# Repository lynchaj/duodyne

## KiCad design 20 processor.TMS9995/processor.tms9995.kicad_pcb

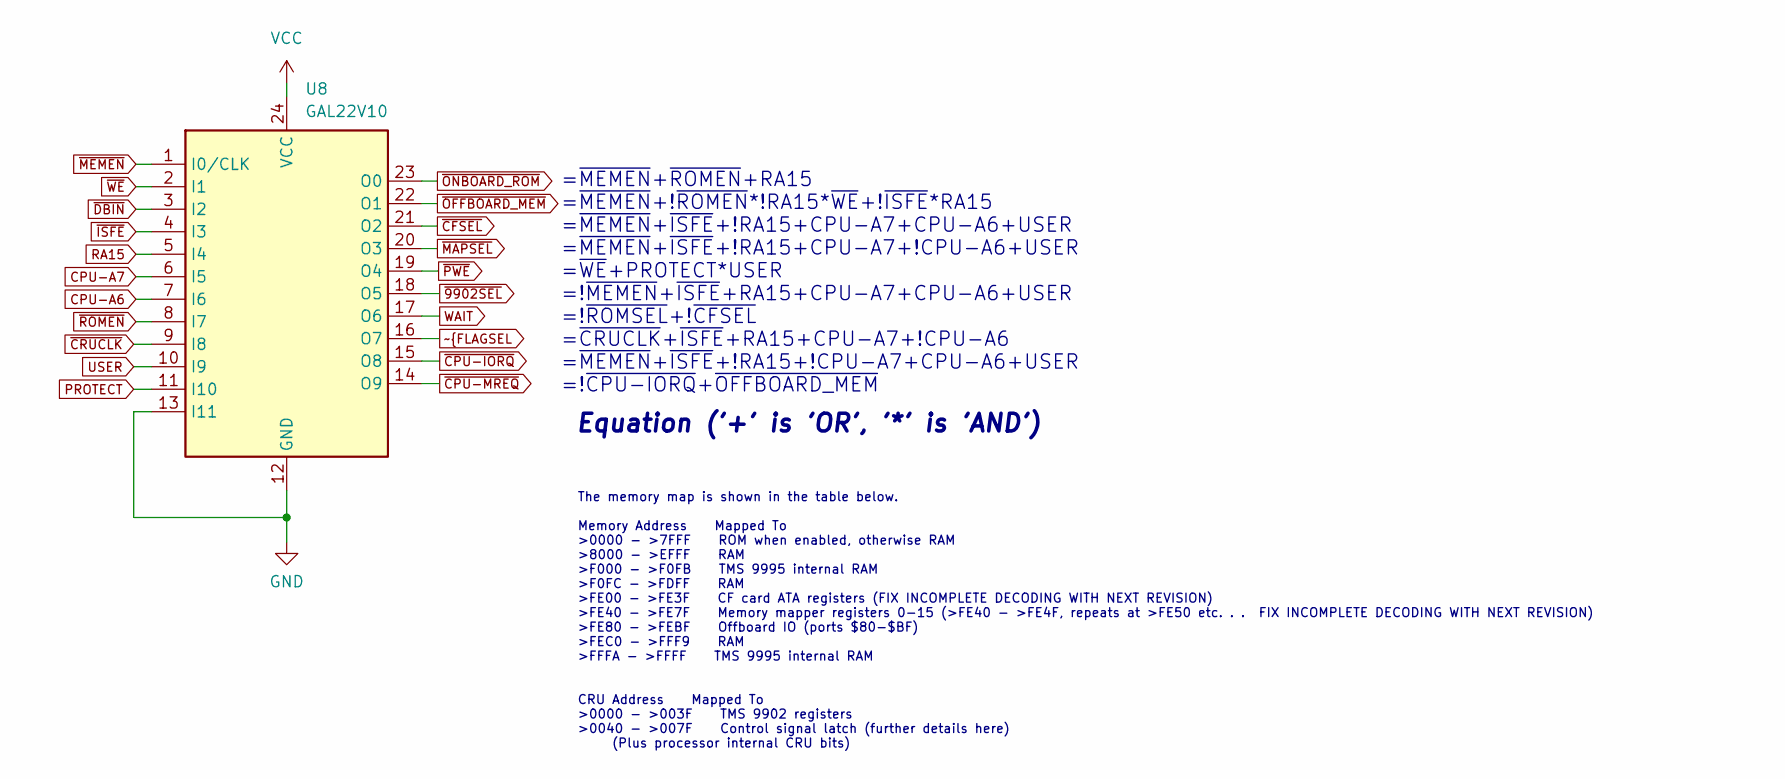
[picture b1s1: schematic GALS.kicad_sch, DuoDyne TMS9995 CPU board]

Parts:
U8: GAL22V10; DIP-24_W7.62mm_Socket_LongPads

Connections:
CPU-A6: U8.7 (I6); also elsewhere on the board
CPU-A7: U8.6 (I5); also elsewhere on the board
GND: U8.12 (GND), U8.13 (I11); also elsewhere on the board
PROTECT: U8.11 (I10); also elsewhere on the board
RA15: U8.5 (I4); also elsewhere on the board
USER: U8.10 (I9); also elsewhere on the board
VCC: U8.24 (VCC); also elsewhere on the board
WAIT: U8.17 (O6); also elsewhere on the board
~9902SEL: U8.18 (O5); also elsewhere on the board
~CFSEL: U8.21 (O2); also elsewhere on the board
~CPU-IORQ: U8.15 (O8); also elsewhere on the board
~CPU-MREQ: U8.14 (O9); also elsewhere on the board
~CRUCLK: U8.9 (I8); also elsewhere on the board
~DBIN: U8.3 (I2); also elsewhere on the board
~ISFE: U8.4 (I3); also elsewhere on the board
~MAPSEL: U8.20 (O3); also elsewhere on the board
~MEMEN: U8.1 (I0/CLK); also elsewhere on the board
~OFFBOARD_MEM: U8.22 (O1); also elsewhere on the board
~ONBOARD_ROM: U8.23 (O0); also elsewhere on the board
~PWE: U8.19 (O4); also elsewhere on the board
~ROMEN: U8.8 (I7); also elsewhere on the board
~WE: U8.2 (I1); also elsewhere on the board

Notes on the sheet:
=~{MEMEN}+~{ROMEN}+RA15 =~{MEMEN}+!~{ROMEN}*!RA15*~{WE}+!~{ISFE}*RA15 =~{MEMEN}+~{ISFE}+!RA15+CPU-A7+CPU-A6+USER =~{MEMEN}+~{ISFE}+!RA15+CPU-A7+!CPU-A6+USER =~{WE}+PROTECT*USER =!~{MEMEN}+~{ISFE}+RA15+CPU-A7+CPU-A6+USER =!~{ROMSEL}+!~{CFSEL} =~{CRUCLK}+~{ISFE}+RA15+CPU-A7+!CPU-A6 =~{MEMEN}+~{ISFE}+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
Equation ('+' is 'OR', '*' is 'AND')
The memory map is shown in the table below. Memory Address Mapped To >0000 - >7FFF ROM when enabled, otherwise RAM >8000 - >EFFF RAM >F000 - >F0FB TMS 9995 internal RAM >F0FC - >FDFF RAM >FE00 - >FE3F CF card ATA registers (FIX INCOMPLETE DECODING WITH NEXT REVISION) >FE40 - >FE7F Memory mapper reg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

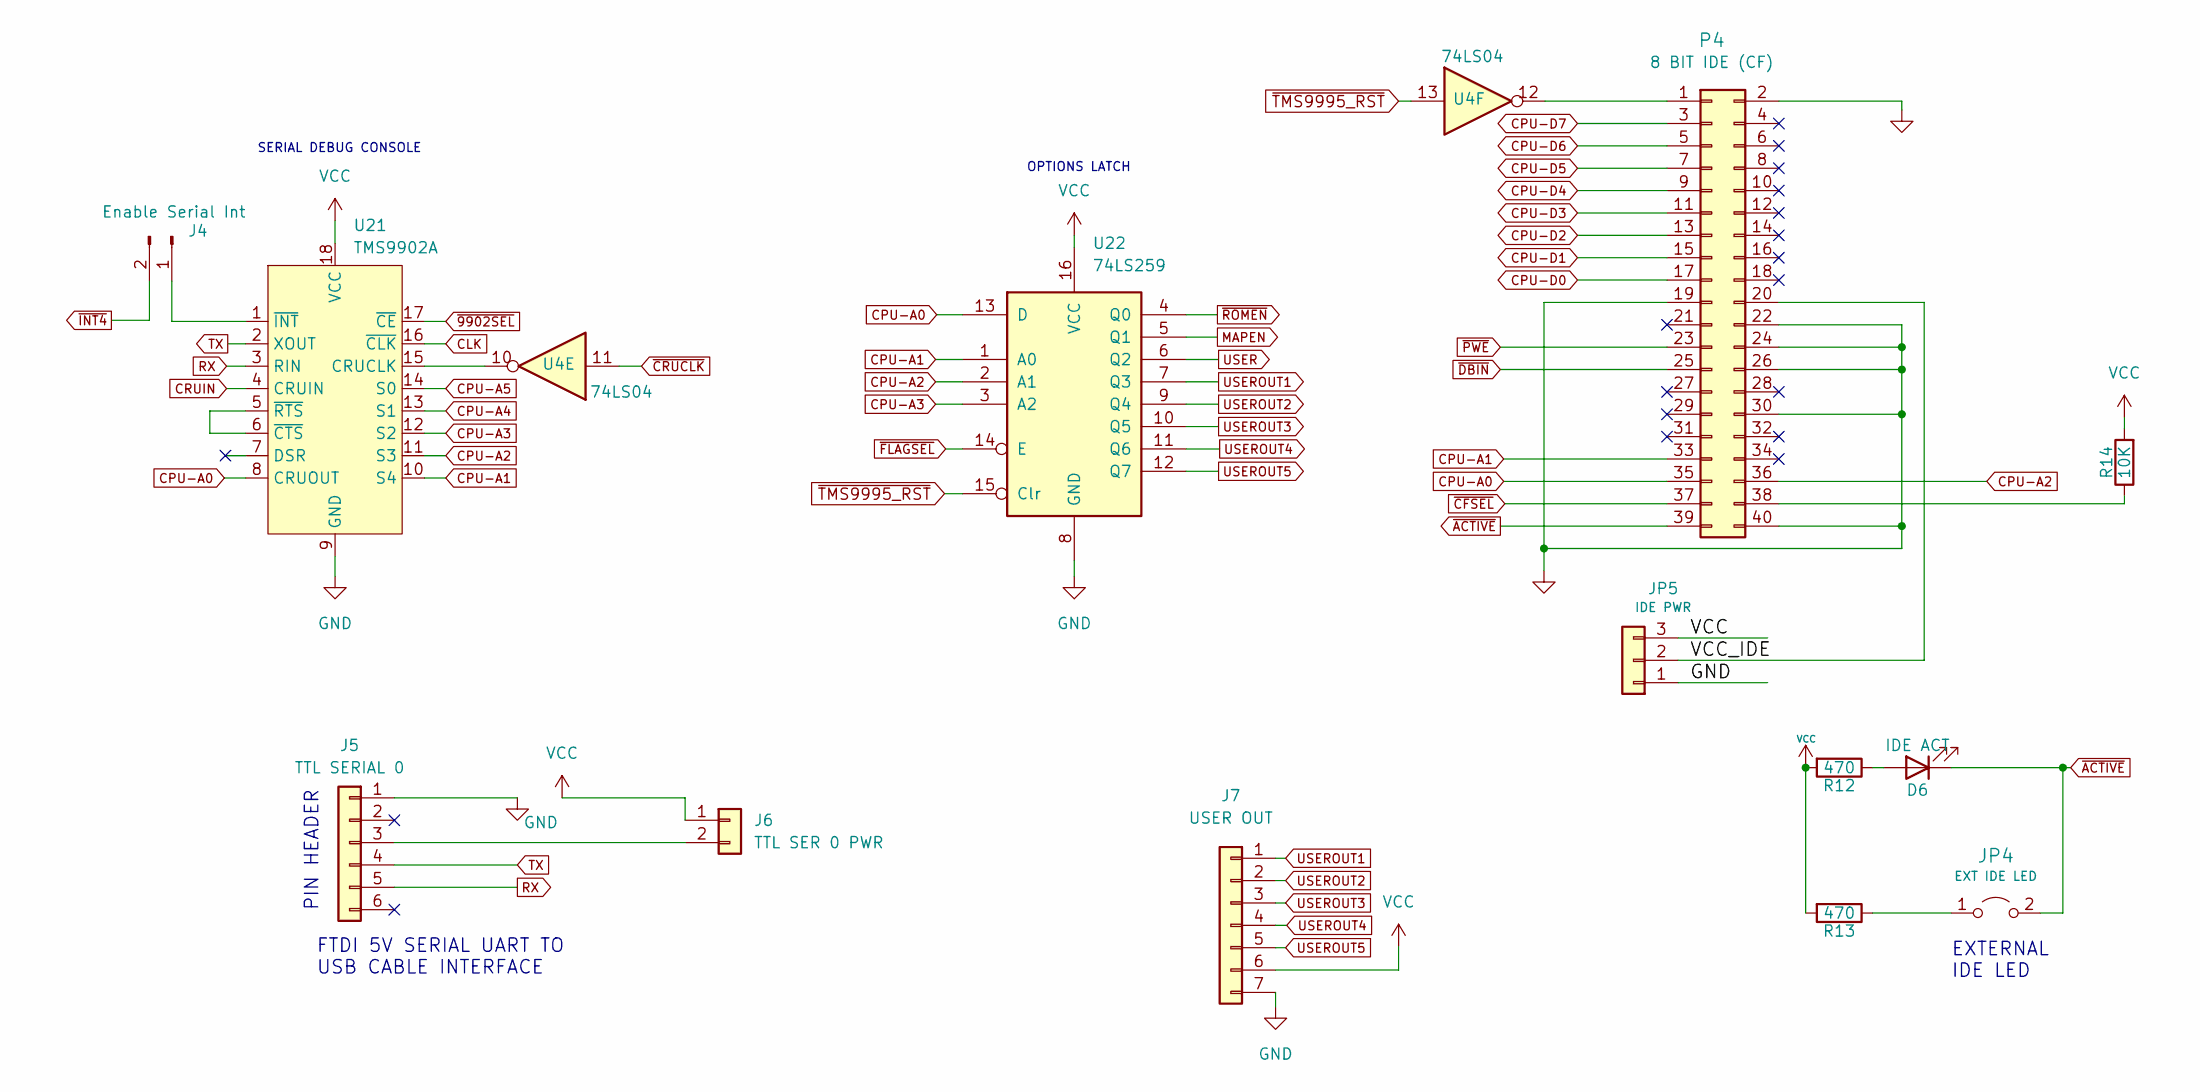
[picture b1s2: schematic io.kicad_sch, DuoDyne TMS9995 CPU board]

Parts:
D6: IDE ACT; LED_D3.0mm_Horizontal_O3.81mm_Z2.0mm
J4: Enable Serial Int; PinHeader_1x02_P2.54mm_Vertical
J5: TTL SERIAL 0; PinHeader_1x06_P2.54mm_Horizontal
J6: TTL SER 0 PWR; PinHeader_1x02_P2.54mm_Vertical
J7: USER OUT; PinHeader_1x07_P2.54mm_Horizontal
JP4: EXT IDE LED; PinHeader_1x02_P2.54mm_Vertical
JP5: IDE PWR; PinHeader_1x03_P2.54mm_Vertical
P4: 8 BIT IDE (CF); IDC-Header_2x20_P2.54mm_Horizontal
R12, R13: 470; R_Axial_DIN0207_L6.3mm_D2.5mm_P7.62mm_Horizontal
R14: 10K; R_Axial_DIN0207_L6.3mm_D2.5mm_P7.62mm_Horizontal
U4: 74LS04; DIP-14_W7.62mm_Socket_LongPads
U21: TMS9902A; DIP-18_W7.62mm_Socket_LongPads
U22: 74LS259; DIP-16_W7.62mm_Socket_LongPads

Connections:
/IO/VCC_IDE: JP5.2, P4.20
CLK: U21.16 (~CLK); also elsewhere on the board
CPU-A0: P4.35, U21.8 (CRUOUT), U22.13 (D); also elsewhere on the board
CPU-A1: P4.33, U21.10 (S4), U22.1 (A0); also elsewhere on the board
CPU-A2: P4.36, U21.11 (S3), U22.2 (A1); also elsewhere on the board
CPU-A3: U21.12 (S2), U22.3 (A2); also elsewhere on the board
CPU-A4: U21.13 (S1); also elsewhere on the board
CPU-A5: U21.14 (S0); also elsewhere on the board
CPU-D0: P4.17; also elsewhere on the board
CPU-D1: P4.15; also elsewhere on the board
CPU-D2: P4.13; also elsewhere on the board
CPU-D3: P4.11; also elsewhere on the board
CPU-D4: P4.9; also elsewhere on the board
CPU-D5: P4.7; also elsewhere on the board
CPU-D6: P4.5; also elsewhere on the board
CPU-D7: P4.3; also elsewhere on the board
CRUIN: U21.4 (CRUIN); also elsewhere on the board
GND: J5.1, J7.7, JP5.1, P4.2, P4.19, P4.22, P4.24, P4.26, P4.30, P4.40, U21.9 (GND), U22.8 (GND); also elsewhere on the board
MAPEN: U22.5 (Q1); also elsewhere on the board
unnamed: D6.2 (A), R12.1
unnamed: J4.1, U21.1 (~INT)
unnamed: J5.3, J6.2
unnamed: JP4.1 (A), R13.1
unnamed: P4.1, U4.12
unnamed: P4.38, R14.1
unnamed: U21.5 (~RTS), U21.6 (~CTS)
unnamed: U4.10, U21.15 (CRUCLK)
RX: J5.5, U21.3 (RIN)
TX: J5.4, U21.2 (XOUT)
USER: U22.6 (Q2); also elsewhere on the board
USEROUT1: J7.1, U22.7 (Q3)
USEROUT2: J7.2, U22.9 (Q4)
USEROUT3: J7.3, U22.10 (Q5)
USEROUT4: J7.4, U22.11 (Q6)
USEROUT5: J7.5, U22.12 (Q7)
VCC: J6.1, J7.6, JP5.3, R12.2, R13.2, R14.2, U21.18 (VCC), U22.16 (VCC); also elsewhere on the board
~9902SEL: U21.17 (~CE); also elsewhere on the board
~ACTIVE: D6.1 (K), JP4.2 (B), P4.39
~CFSEL: P4.37; also elsewhere on the board
~CRUCLK: U4.11; also elsewhere on the board
~DBIN: P4.25; also elsewhere on the board
~INT4: J4.2; also elsewhere on the board
~PWE: P4.23; also elsewhere on the board
~ROMEN: U22.4 (Q0); also elsewhere on the board
~TMS9995_RST: U4.13, U22.15 (Clr); also elsewhere on the board

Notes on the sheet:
PIN HEADER
EXTERNAL IDE LED
FTDI 5V SERIAL UART TO USB CABLE INTERFACE
SERIAL DEBUG CONSOLE
OPTIONS LATCH

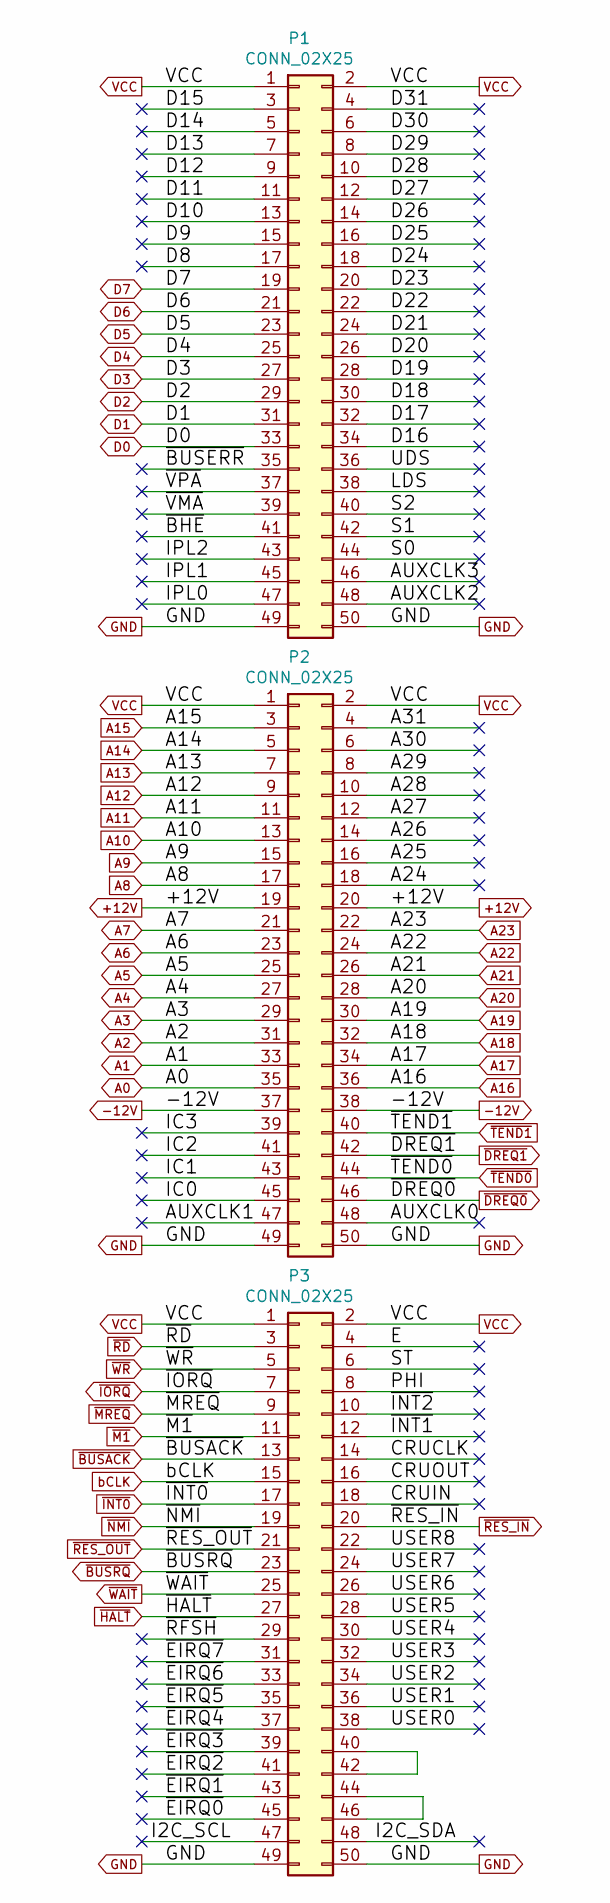
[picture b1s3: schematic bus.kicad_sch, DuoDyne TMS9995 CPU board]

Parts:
P1, P2, P3: CONN_02X25; IDC-Header_2x25_P2.54mm_Horizontal

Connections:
+12V: P2.19, P2.20
-12V: P2.37, P2.38
/bus/A24: P2.18
/bus/A25: P2.16
/bus/A26: P2.14
/bus/A27: P2.12
/bus/A28: P2.10
/bus/A29: P2.8
/bus/A30: P2.6
/bus/A31: P2.4
/bus/AUXCLK0: P2.48
/bus/AUXCLK1: P2.47
/bus/AUXCLK2: P1.48
/bus/AUXCLK3: P1.46
/bus/CRUCLK: P3.14
/bus/CRUIN: P3.18
/bus/CRUOUT: P3.16
/bus/D8: P1.17
/bus/D9: P1.15
/bus/D10: P1.13
/bus/D11: P1.11
/bus/D12: P1.9
/bus/D13: P1.7
/bus/D14: P1.5
/bus/D15: P1.3
/bus/D16: P1.34
/bus/D17: P1.32
/bus/D18: P1.30
/bus/D19: P1.28
/bus/D20: P1.26
/bus/D21: P1.24
/bus/D22: P1.22
/bus/D23: P1.20
/bus/D24: P1.18
/bus/D25: P1.16
/bus/D26: P1.14
/bus/D27: P1.12
/bus/D28: P1.10
/bus/D29: P1.8
/bus/D30: P1.6
/bus/D31: P1.4
/bus/E: P3.4
/bus/I2C_SCL: P3.47
/bus/I2C_SDA: P3.48
/bus/IC0: P2.45
/bus/IC1: P2.43
/bus/IC2: P2.41
/bus/IC3: P2.39
/bus/IPL0: P1.47
/bus/IPL1: P1.45
/bus/IPL2: P1.43
/bus/LDS: P1.38
/bus/PHI: P3.8
/bus/S0: P1.44
/bus/S1: P1.42
/bus/S2: P1.40
/bus/ST: P3.6
/bus/UDS: P1.36
/bus/USER0: P3.38
/bus/USER1: P3.36
/bus/USER2: P3.34
/bus/USER3: P3.32
/bus/USER4: P3.30
/bus/USER5: P3.28
/bus/USER6: P3.26
/bus/USER7: P3.24
/bus/USER8: P3.22
/bus/~BHE: P1.41
/bus/~BUSERR: P1.35
/bus/~EIRQ0: P3.45
/bus/~EIRQ1: P3.43
/bus/~EIRQ2: P3.41
/bus/~EIRQ3: P3.39
/bus/~EIRQ4: P3.37
/bus/~EIRQ5: P3.35
/bus/~EIRQ6: P3.33
/bus/~EIRQ7: P3.31
/bus/~INT1: P3.12
/bus/~INT2: P3.10
/bus/~RFSH: P3.29
/bus/~VMA: P1.39
/bus/~VPA: P1.37
A0: P2.35; also elsewhere on the board
A1: P2.33; also elsewhere on the board
A2: P2.31; also elsewhere on the board
A3: P2.29; also elsewhere on the board
A4: P2.27; also elsewhere on the board
A5: P2.25; also elsewhere on the board
A6: P2.23; also elsewhere on the board
A7: P2.21; also elsewhere on the board
A8: P2.17; also elsewhere on the board
A9: P2.15; also elsewhere on the board
A10: P2.13; also elsewhere on the board
A11: P2.11; also elsewhere on the board
A12: P2.9; also elsewhere on the board
A13: P2.7; also elsewhere on the board
A14: P2.5; also elsewhere on the board
A15: P2.3; also elsewhere on the board
A16: P2.36; also elsewhere on the board
A17: P2.34; also elsewhere on the board
A18: P2.32; also elsewhere on the board
A19: P2.30; also elsewhere on the board
A20: P2.28; also elsewhere on the board
A21: P2.26; also elsewhere on the board
A22: P2.24; also elsewhere on the board
A23: P2.22; also elsewhere on the board
D0: P1.33; also elsewhere on the board
D1: P1.31; also elsewhere on the board
D2: P1.29; also elsewhere on the board
D3: P1.27; also elsewhere on the board
D4: P1.25; also elsewhere on the board
D5: P1.23; also elsewhere on the board
D6: P1.21; also elsewhere on the board
D7: P1.19; also elsewhere on the board
GND: P1.49, P1.50, P2.49, P2.50, P3.49, P3.50; also elsewhere on the board
unnamed: P3.40, P3.42
unnamed: P3.44, P3.46
VCC: P1.1, P1.2, P2.1, P2.2, P3.1, P3.2; also elsewhere on the board
bCLK: P3.15; also elsewhere on the board
~BUSACK: P3.13; also elsewhere on the board
~BUSRQ: P3.23; also elsewhere on the board
~DREQ0: P2.46; also elsewhere on the board
~DREQ1: P2.42; also elsewhere on the board
~HALT: P3.27; also elsewhere on the board
~INT0: P3.17; also elsewhere on the board
~IORQ: P3.7; also elsewhere on the board
~M1: P3.11; also elsewhere on the board
~MREQ: P3.9; also elsewhere on the board
~NMI: P3.19; also elsewhere on the board
~RD: P3.3; also elsewhere on the board
~RES_IN: P3.20; also elsewhere on the board
~RES_OUT: P3.21; also elsewhere on the board
~TEND0: P2.44; also elsewhere on the board
~TEND1: P2.40; also elsewhere on the board
~WAIT: P3.25; also elsewhere on the board
~WR: P3.5; also elsewhere on the board

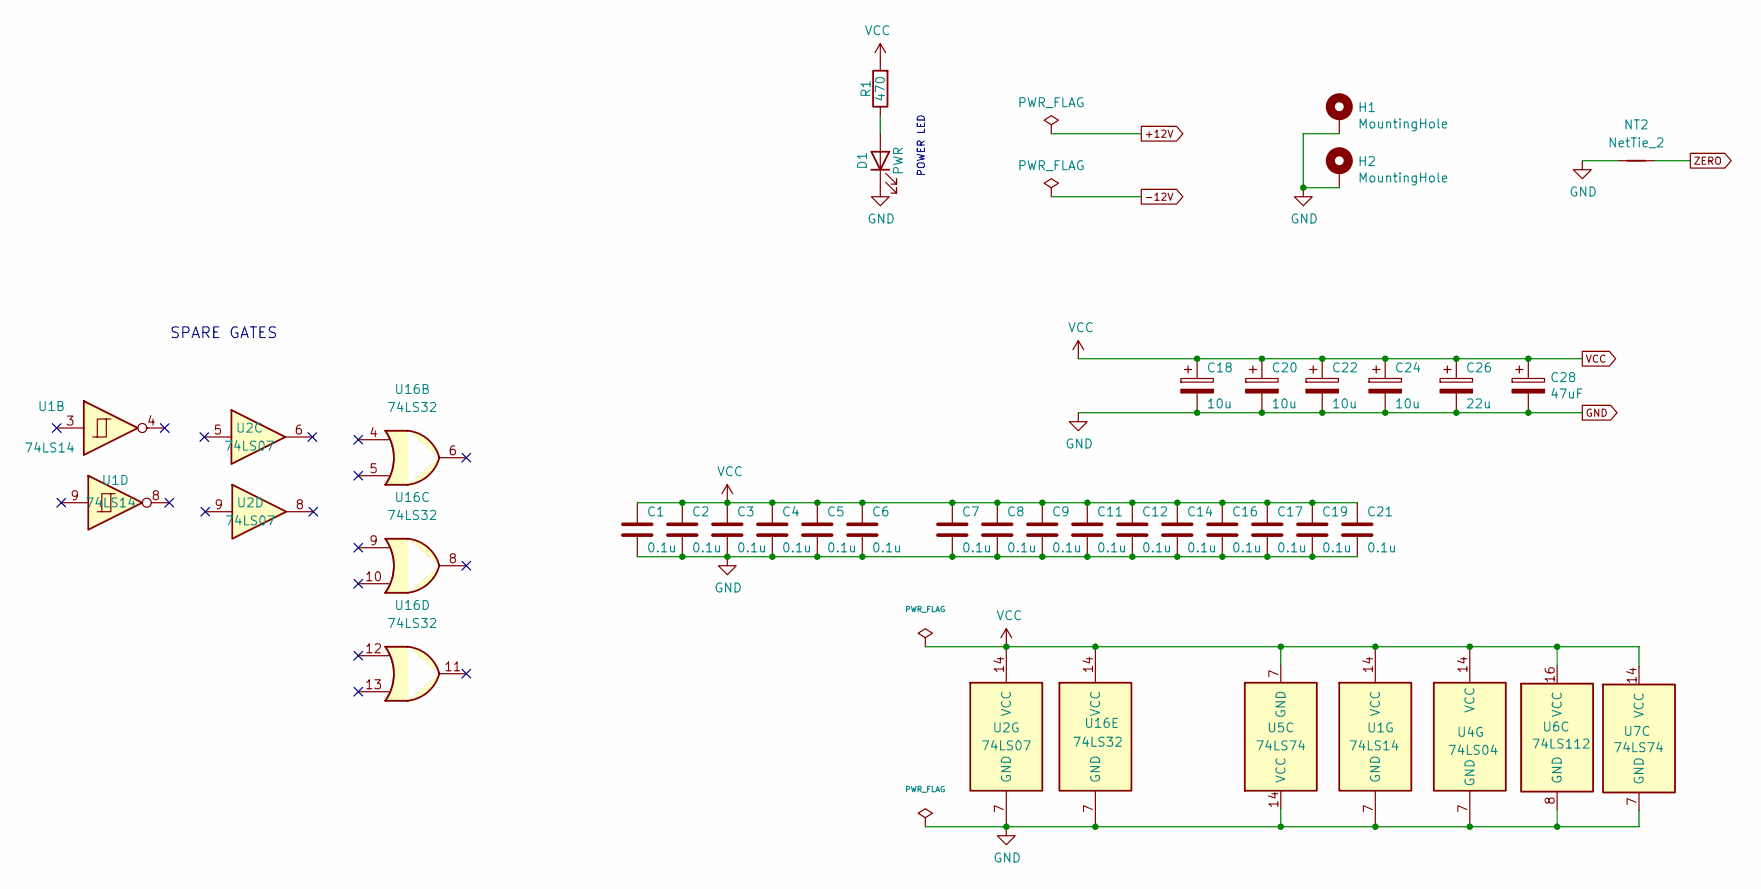
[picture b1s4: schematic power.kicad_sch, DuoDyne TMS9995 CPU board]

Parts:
C1, C2, C3, C4, C5, C6, C7, C8, C9, C11, C12, C14, C16, C17, C19, C21: 0.1u; C_Disc_D5.0mm_W2.5mm_P5.00mm
C18, C20, C22, C24: 10u; CP_Radial_D5.0mm_P2.50mm
C26: 22u; CP_Radial_D5.0mm_P2.50mm
C28: 47uF; CP_Radial_D5.0mm_P2.50mm
D1: PWR; LED_D3.0mm_Horizontal_O3.81mm_Z2.0mm
H1, H2: MountingHole; MountingHole_3.2mm_M3_Pad
NT2: NetTie_2; NetTie-2_THT_Pad0.3mm
R1: 470; R_Axial_DIN0207_L6.3mm_D2.5mm_P7.62mm_Horizontal
U1: 74LS14; DIP-14_W7.62mm_Socket_LongPads
U2: 74LS07; DIP-14_W7.62mm_Socket_LongPads
U4: 74LS04; DIP-14_W7.62mm_Socket_LongPads
U5, U7: 74LS74; DIP-14_W7.62mm_Socket_LongPads
U6: 74LS112; DIP-16_W7.62mm_Socket_LongPads
U16: 74LS32; DIP-14_W7.62mm_Socket_LongPads

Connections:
GND: C1.2, C2.2, C3.2, C4.2, C5.2, C6.2, C7.2, C8.2, C9.2, C11.2, C12.2, C14.2, C16.2, C17.2, C18.2, C19.2, C20.2, C21.2, C22.2, C24.2, C26.2, C28.2, D1.1 (K), H1.1, H2.1, NT2.1, U1.7 (GND), U2.7 (GND), U4.7 (GND), U5.14 (VCC), U6.8 (GND), U7.7 (GND), U16.7 (GND); also elsewhere on the board
unnamed: D1.2 (A), R1.1
VCC: C1.1, C2.1, C3.1, C4.1, C5.1, C6.1, C7.1, C8.1, C9.1, C11.1, C12.1, C14.1, C16.1, C17.1, C18.1, C19.1, C20.1, C21.1, C22.1, C24.1, C26.1, C28.1, R1.2, U1.14 (VCC), U2.14 (VCC), U4.14 (VCC), U5.7 (GND), U6.16 (VCC), U7.14 (VCC), U16.14 (VCC); also elsewhere on the board
ZERO: NT2.2; also elsewhere on the board

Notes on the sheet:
POWER LED
SPARE GATES

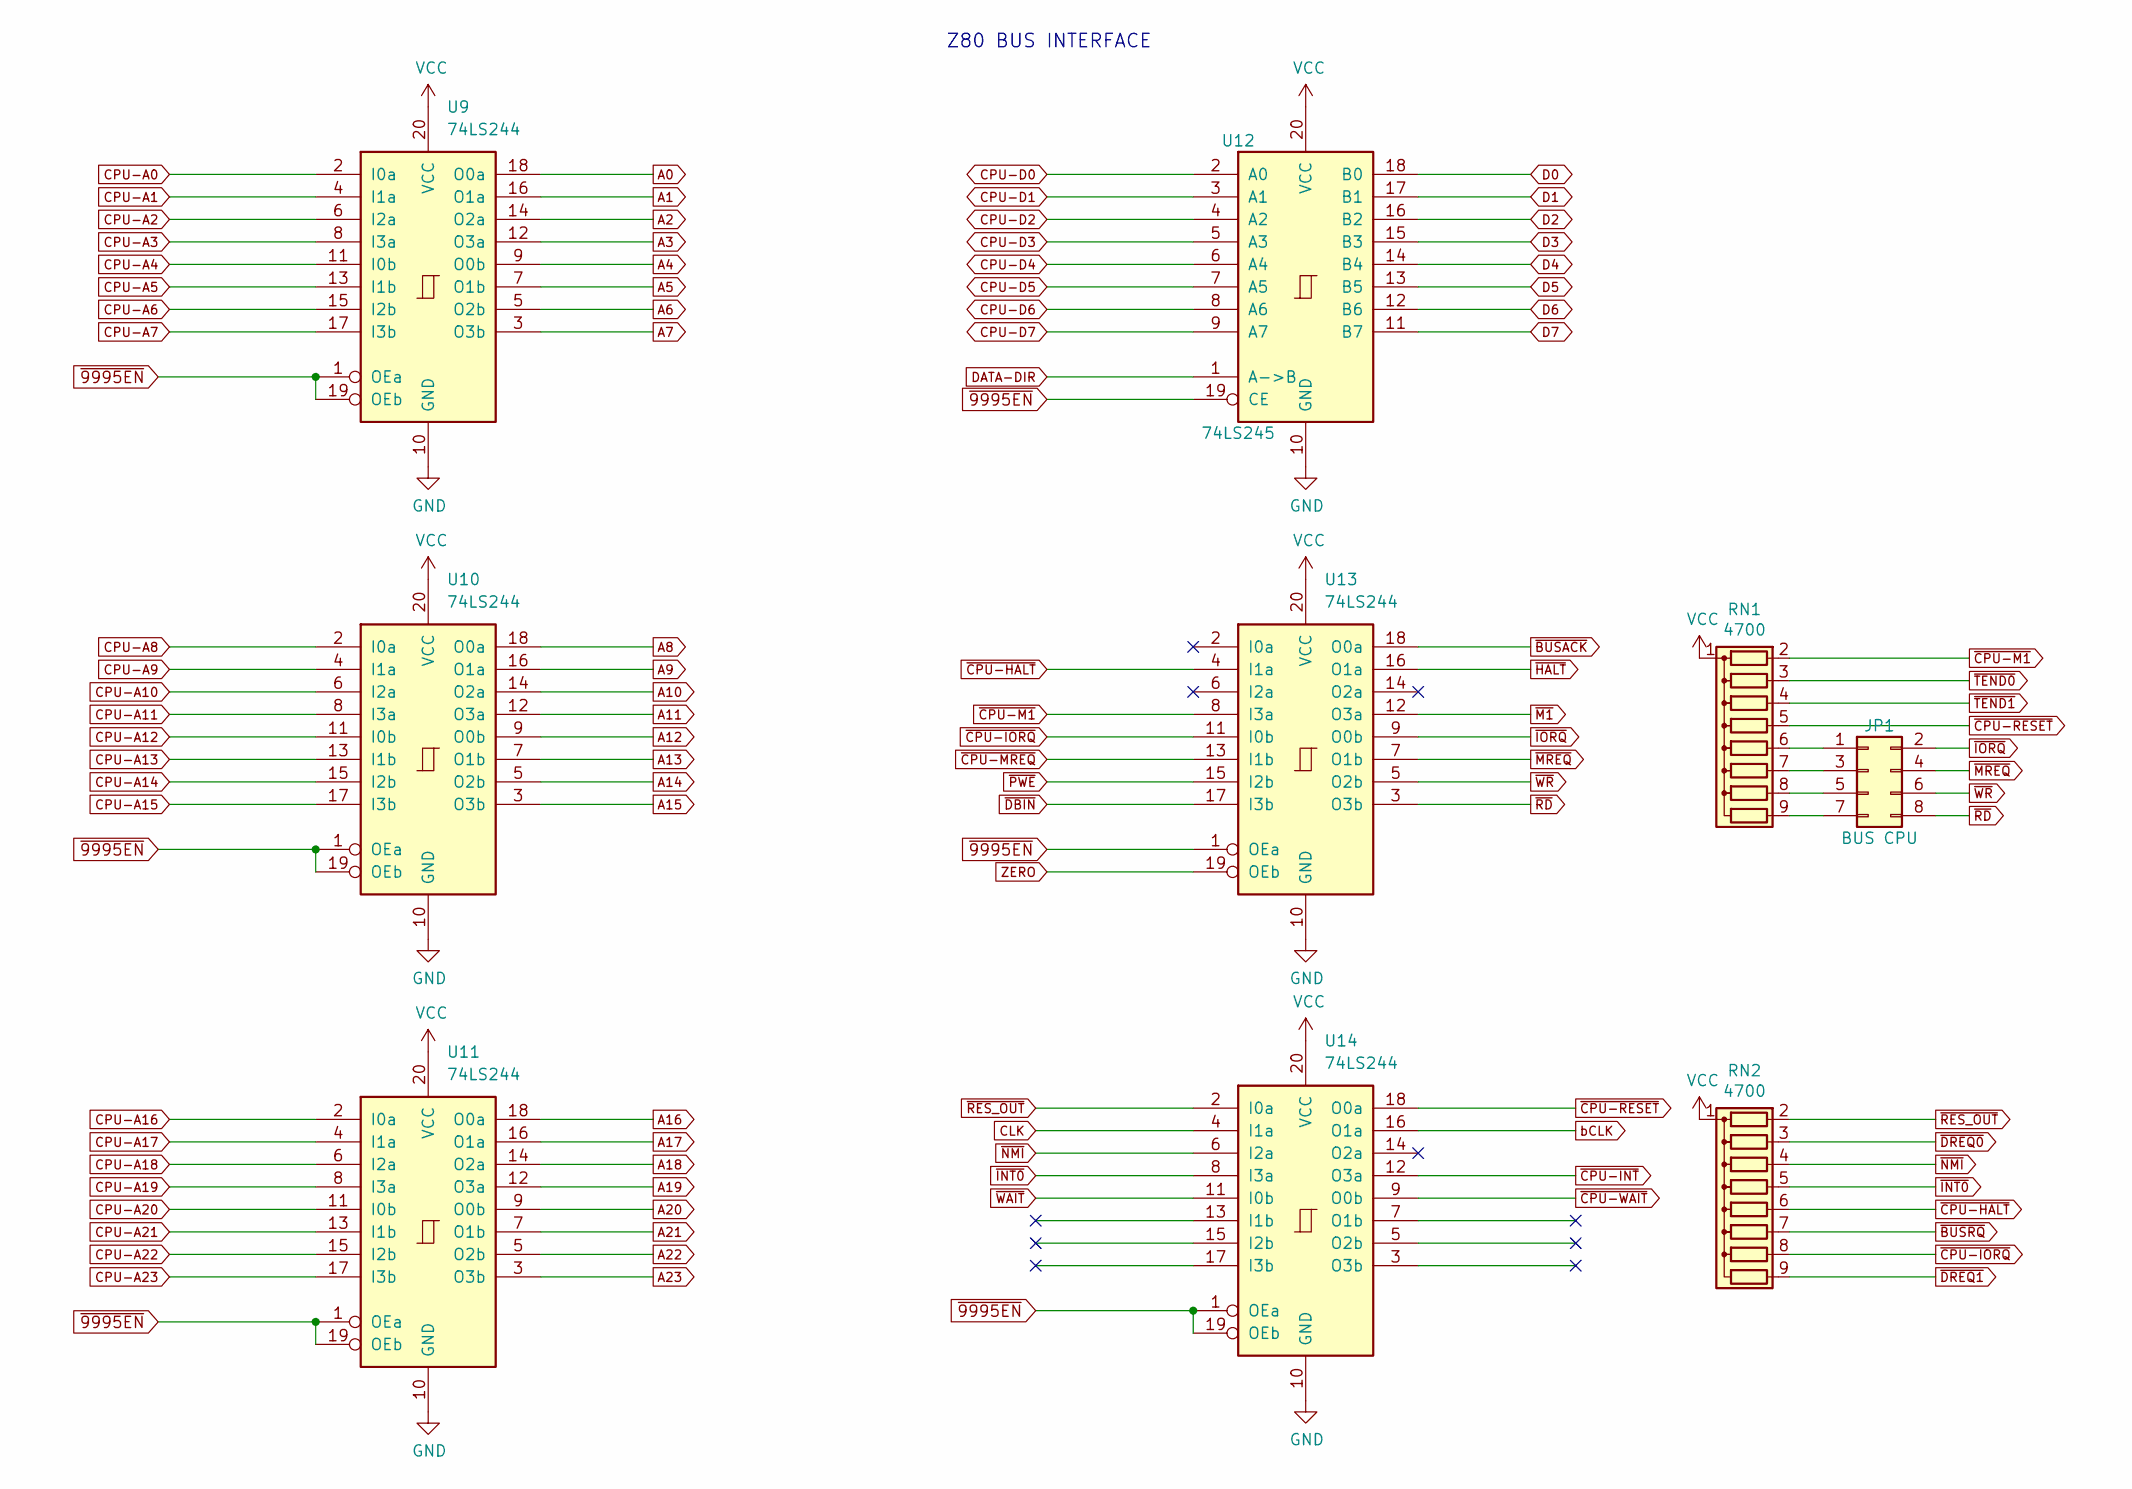
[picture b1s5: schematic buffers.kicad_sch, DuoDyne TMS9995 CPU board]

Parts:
JP1: BUS CPU; PinHeader_2x04_P2.54mm_Vertical
RN1, RN2: 4700; R_Array_SIP9
U9, U10, U11, U13, U14: 74LS244; DIP-20_W7.62mm_Socket_LongPads
U12: 74LS245; DIP-20_W7.62mm_Socket_LongPads

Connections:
A0: U9.18 (O0a); also elsewhere on the board
A1: U9.16 (O1a); also elsewhere on the board
A2: U9.14 (O2a); also elsewhere on the board
A3: U9.12 (O3a); also elsewhere on the board
A4: U9.9 (O0b); also elsewhere on the board
A5: U9.7 (O1b); also elsewhere on the board
A6: U9.5 (O2b); also elsewhere on the board
A7: U9.3 (O3b); also elsewhere on the board
A8: U10.18 (O0a); also elsewhere on the board
A9: U10.16 (O1a); also elsewhere on the board
A10: U10.14 (O2a); also elsewhere on the board
A11: U10.12 (O3a); also elsewhere on the board
A12: U10.9 (O0b); also elsewhere on the board
A13: U10.7 (O1b); also elsewhere on the board
A14: U10.5 (O2b); also elsewhere on the board
A15: U10.3 (O3b); also elsewhere on the board
A16: U11.18 (O0a); also elsewhere on the board
A17: U11.16 (O1a); also elsewhere on the board
A18: U11.14 (O2a); also elsewhere on the board
A19: U11.12 (O3a); also elsewhere on the board
A20: U11.9 (O0b); also elsewhere on the board
A21: U11.7 (O1b); also elsewhere on the board
A22: U11.5 (O2b); also elsewhere on the board
A23: U11.3 (O3b); also elsewhere on the board
CLK: U14.4 (I1a); also elsewhere on the board
CPU-A0: U9.2 (I0a); also elsewhere on the board
CPU-A1: U9.4 (I1a); also elsewhere on the board
CPU-A2: U9.6 (I2a); also elsewhere on the board
CPU-A3: U9.8 (I3a); also elsewhere on the board
CPU-A4: U9.11 (I0b); also elsewhere on the board
CPU-A5: U9.13 (I1b); also elsewhere on the board
CPU-A6: U9.15 (I2b); also elsewhere on the board
CPU-A7: U9.17 (I3b); also elsewhere on the board
CPU-A8: U10.2 (I0a); also elsewhere on the board
CPU-A9: U10.4 (I1a); also elsewhere on the board
CPU-A10: U10.6 (I2a); also elsewhere on the board
CPU-A11: U10.8 (I3a); also elsewhere on the board
CPU-A12: U10.11 (I0b); also elsewhere on the board
CPU-A13: U10.13 (I1b); also elsewhere on the board
CPU-A14: U10.15 (I2b); also elsewhere on the board
CPU-A15: U10.17 (I3b); also elsewhere on the board
CPU-A16: U11.2 (I0a); also elsewhere on the board
CPU-A17: U11.4 (I1a); also elsewhere on the board
CPU-A18: U11.6 (I2a); also elsewhere on the board
CPU-A19: U11.8 (I3a); also elsewhere on the board
CPU-A20: U11.11 (I0b); also elsewhere on the board
CPU-A21: U11.13 (I1b); also elsewhere on the board
CPU-A22: U11.15 (I2b); also elsewhere on the board
CPU-A23: U11.17 (I3b); also elsewhere on the board
CPU-D0: U12.2 (A0); also elsewhere on the board
CPU-D1: U12.3 (A1); also elsewhere on the board
CPU-D2: U12.4 (A2); also elsewhere on the board
CPU-D3: U12.5 (A3); also elsewhere on the board
CPU-D4: U12.6 (A4); also elsewhere on the board
CPU-D5: U12.7 (A5); also elsewhere on the board
CPU-D6: U12.8 (A6); also elsewhere on the board
CPU-D7: U12.9 (A7); also elsewhere on the board
D0: U12.18 (B0); also elsewhere on the board
D1: U12.17 (B1); also elsewhere on the board
D2: U12.16 (B2); also elsewhere on the board
D3: U12.15 (B3); also elsewhere on the board
D4: U12.14 (B4); also elsewhere on the board
D5: U12.13 (B5); also elsewhere on the board
D6: U12.12 (B6); also elsewhere on the board
D7: U12.11 (B7); also elsewhere on the board
DATA-DIR: U12.1 (A->B); also elsewhere on the board
GND: U9.10 (GND), U10.10 (GND), U11.10 (GND), U12.10 (GND), U13.10 (GND), U14.10 (GND); also elsewhere on the board
unnamed: JP1.1, RN1.6 (R5)
unnamed: JP1.3, RN1.7 (R6)
unnamed: JP1.5, RN1.8 (R7)
unnamed: JP1.7, RN1.9 (R8)
VCC: RN1.1 (common), RN2.1 (common), U9.20 (VCC), U10.20 (VCC), U11.20 (VCC), U12.20 (VCC), U13.20 (VCC), U14.20 (VCC); also elsewhere on the board
ZERO: U13.19 (OEb); also elsewhere on the board
bCLK: U14.16 (O1a); also elsewhere on the board
~9995EN: U9.1 (OEa), U9.19 (OEb), U10.1 (OEa), U10.19 (OEb), U11.1 (OEa), U11.19 (OEb), U12.19 (CE), U13.1 (OEa), U14.1 (OEa), U14.19 (OEb); also elsewhere on the board
~BUSACK: U13.18 (O0a); also elsewhere on the board
~BUSRQ: RN2.7 (R6); also elsewhere on the board
~CPU-HALT: RN2.6 (R5), U13.4 (I1a)
~CPU-INT: U14.12 (O3a); also elsewhere on the board
~CPU-IORQ: RN2.8 (R7), U13.11 (I0b); also elsewhere on the board
~CPU-M1: RN1.2 (R1), U13.8 (I3a)
~CPU-MREQ: U13.13 (I1b); also elsewhere on the board
~CPU-RESET: RN1.5 (R4), U14.18 (O0a)
~CPU-WAIT: U14.9 (O0b); also elsewhere on the board
~DBIN: U13.17 (I3b); also elsewhere on the board
~DREQ0: RN2.3 (R2); also elsewhere on the board
~DREQ1: RN2.9 (R8); also elsewhere on the board
~HALT: U13.16 (O1a); also elsewhere on the board
~INT0: RN2.5 (R4), U14.8 (I3a); also elsewhere on the board
~IORQ: JP1.2, U13.9 (O0b); also elsewhere on the board
~M1: U13.12 (O3a); also elsewhere on the board
~MREQ: JP1.4, U13.7 (O1b); also elsewhere on the board
~NMI: RN2.4 (R3), U14.6 (I2a); also elsewhere on the board
~PWE: U13.15 (I2b); also elsewhere on the board
~RD: JP1.8, U13.3 (O3b); also elsewhere on the board
~RES_OUT: RN2.2 (R1), U14.2 (I0a); also elsewhere on the board
~TEND0: RN1.3 (R2); also elsewhere on the board
~TEND1: RN1.4 (R3); also elsewhere on the board
~WAIT: U14.11 (I0b); also elsewhere on the board
~WR: JP1.6, U13.5 (O2b); also elsewhere on the board

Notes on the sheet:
Z80 BUS INTERFACE
